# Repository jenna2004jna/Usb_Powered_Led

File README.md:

# USB Powered LED Controller Board

A beginner-friendly KiCAD EDA project: a small through-hole PCB that powers and controls a single LED from USB 5V using a tactile push button. No microcontroller or firmware required — this project teaches the full PCB design workflow (schematic capture, ERC, footprint assignment, layout, 3D validation, and manufacturing output).

Designed by Jenna – Embedded Enthusiast

---

## Key Features

- Powers a single LED from USB-A VBUS (5V)
- Push-button control (press to light)
- Current-limited to ~8–10 mA using a 330 Ω resistor
- 10 kΩ pull-up to keep the LED node defined when switch is open
- 0.1 µF decoupling capacitor on VBUS
- Through-hole components (THT) for easy soldering
- Board size: 40 mm × 20 mm

---

## Operation Summary (Truth Table)

| Switch State | Cathode Node | LED     |
|--------------|--------------|---------|
| Released     | HIGH (5V)    | OFF     |
| Pressed      | LOW (GND)    | ON      |

---

## Components (Reference)

- J1 — USB-A Connector — Connector_USB:USB_A_Horizontal
- D1 — 5 mm LED — LED_THT:LED_D5.0mm
- R1 — 330 Ω — Resistor_THT:R_Axial_DIN0207_P7.62mm
- R2 — 10 kΩ — Resistor_THT:R_Axial_DIN0207_P7.62mm
- SW1 — Tactile Switch 6×6 — Button_Switch_THT:SW_PUSH_6mm
- C1 — 0.1 µF Ceramic — Capacitor_THT:C_Disc_D5.0mm_P2.5mm

---

## Design Rationale (short)

- R1 = 330 Ω gives I ≈ (5V − 2V) / 330 ≈ 9 mA — safe for USB and visible brightness.
- R2 = 10 kΩ keeps the cathode node from floating when the switch is open.
- C1 = 0.1 µF decouples USB VBUS to avoid flicker and suppress noise.
- PWR_FLAG symbols added in schematic to satisfy ERC for power nets.

---

## PCB Design Rules (used)

- Clearance: 0.3 mm
- Power track width: 1.0 mm
- Signal track width: 0.6 mm
- Via drill (if used): 0.6 mm
- Silk clearance: 0.2 mm
- Copper fill tied to GND

---

## Assembly & Bring-Up

1. Solder all through-hole parts (D1, R1, R2, C1, SW1, J1).
2. Inspect soldering and check no shorts on VBUS/GND.
3. Plug in USB cable (5V should appear on VBUS).
4. Press SW1 — D1 should light.
5. Measure:
   - VBUS to GND = ~5.0 V
   - LED current ≈ 8–10 mA (verify with ammeter in series)

Safety note: if LED is unusually bright or current > 20 mA, unplug and re-check R1 value and orientation.

---

## Files in This Project

- schematic.kicad_sch — project schematic
- board.kicad_pcb — PCB layout
- footprints/ — folder with custom footprint assignments (if any)
- fab/ — exported Gerbers & Excellon files
- bom.csv — bill of materials (CSV)
- images/ — example images used below (replace placeholders with your own photos/exports)

---

## Images

Replace the files in `images/` with your exported PNG/JPG files from KiCAD or photos of the assembled board. The README references these four example images:

Figure: Project schematic (exported from KiCAD schematic editor)

Figure: PCB top view showing component placement and routing

Figure: 3D model view from KiCAD 3D viewer (verify part clearances & orientation)

Figure: Photo of the assembled board (optional — useful for documentation)

Tip: export the schematic and PCB views at 300–600 DPI for clear README images; use a 3:2 or 4:3 aspect ratio for nicer layout on README pages.

---

## Generating Manufacturing Outputs

From KiCAD PCB editor:
- File → Fabrication Outputs → Plot → Generate Gerber (Top/Bottom, Silks, Soldermask, etc.)
- File → Fabrication Outputs → Drill Files → Generate Excellon Drill
- Tools → BOM → Generate CSV (or use a plugin for extended BOM)
- Run final DRC and 3D inspection before submission to manufacturer

---

## Notes & Learning Outcomes

This project is ideal for learning:
- KiCAD schematic capture and layout flow
- ERC and DRC workflows
- Footprint matching and pad spacing for THT parts
- Generating fabrication outputs and BOM
- Basic analog reasoning for LED current limiting and pull-ups

---

## License & Credits

- Designed by Jenna – Embedded Enthusiast
- Feel free to reuse and adapt for educational purposes. If you publish derivatives, please credit the original author.

---

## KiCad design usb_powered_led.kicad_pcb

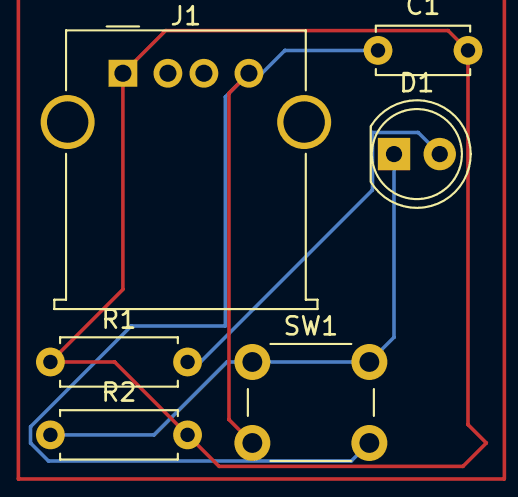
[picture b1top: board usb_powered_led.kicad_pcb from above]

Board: 2 copper layers, 6 parts (0 on the bottom side), 4 nets.

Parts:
C1: 0.1u; C_Disc_D5.0mm_W2.5mm_P5.00mm
D1: LED; LED_D5.0mm
J1: USB_A; USB_A_Molex_67643_Horizontal
R1: 330; R_Axial_DIN0207_L6.3mm_D2.5mm_P7.62mm_Horizontal
R2: 10k; R_Axial_DIN0207_L6.3mm_D2.5mm_P7.62mm_Horizontal
SW1: SW_Push; SW_PUSH_6mm

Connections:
/GND: C1.1, J1.4 (GND), SW1.2
/SW: D1.1 (K), R2.1, SW1.1
/VBUS: C1.2, J1.1 (VBUS), R1.1, R2.2
unnamed: D1.2 (A), R1.2
